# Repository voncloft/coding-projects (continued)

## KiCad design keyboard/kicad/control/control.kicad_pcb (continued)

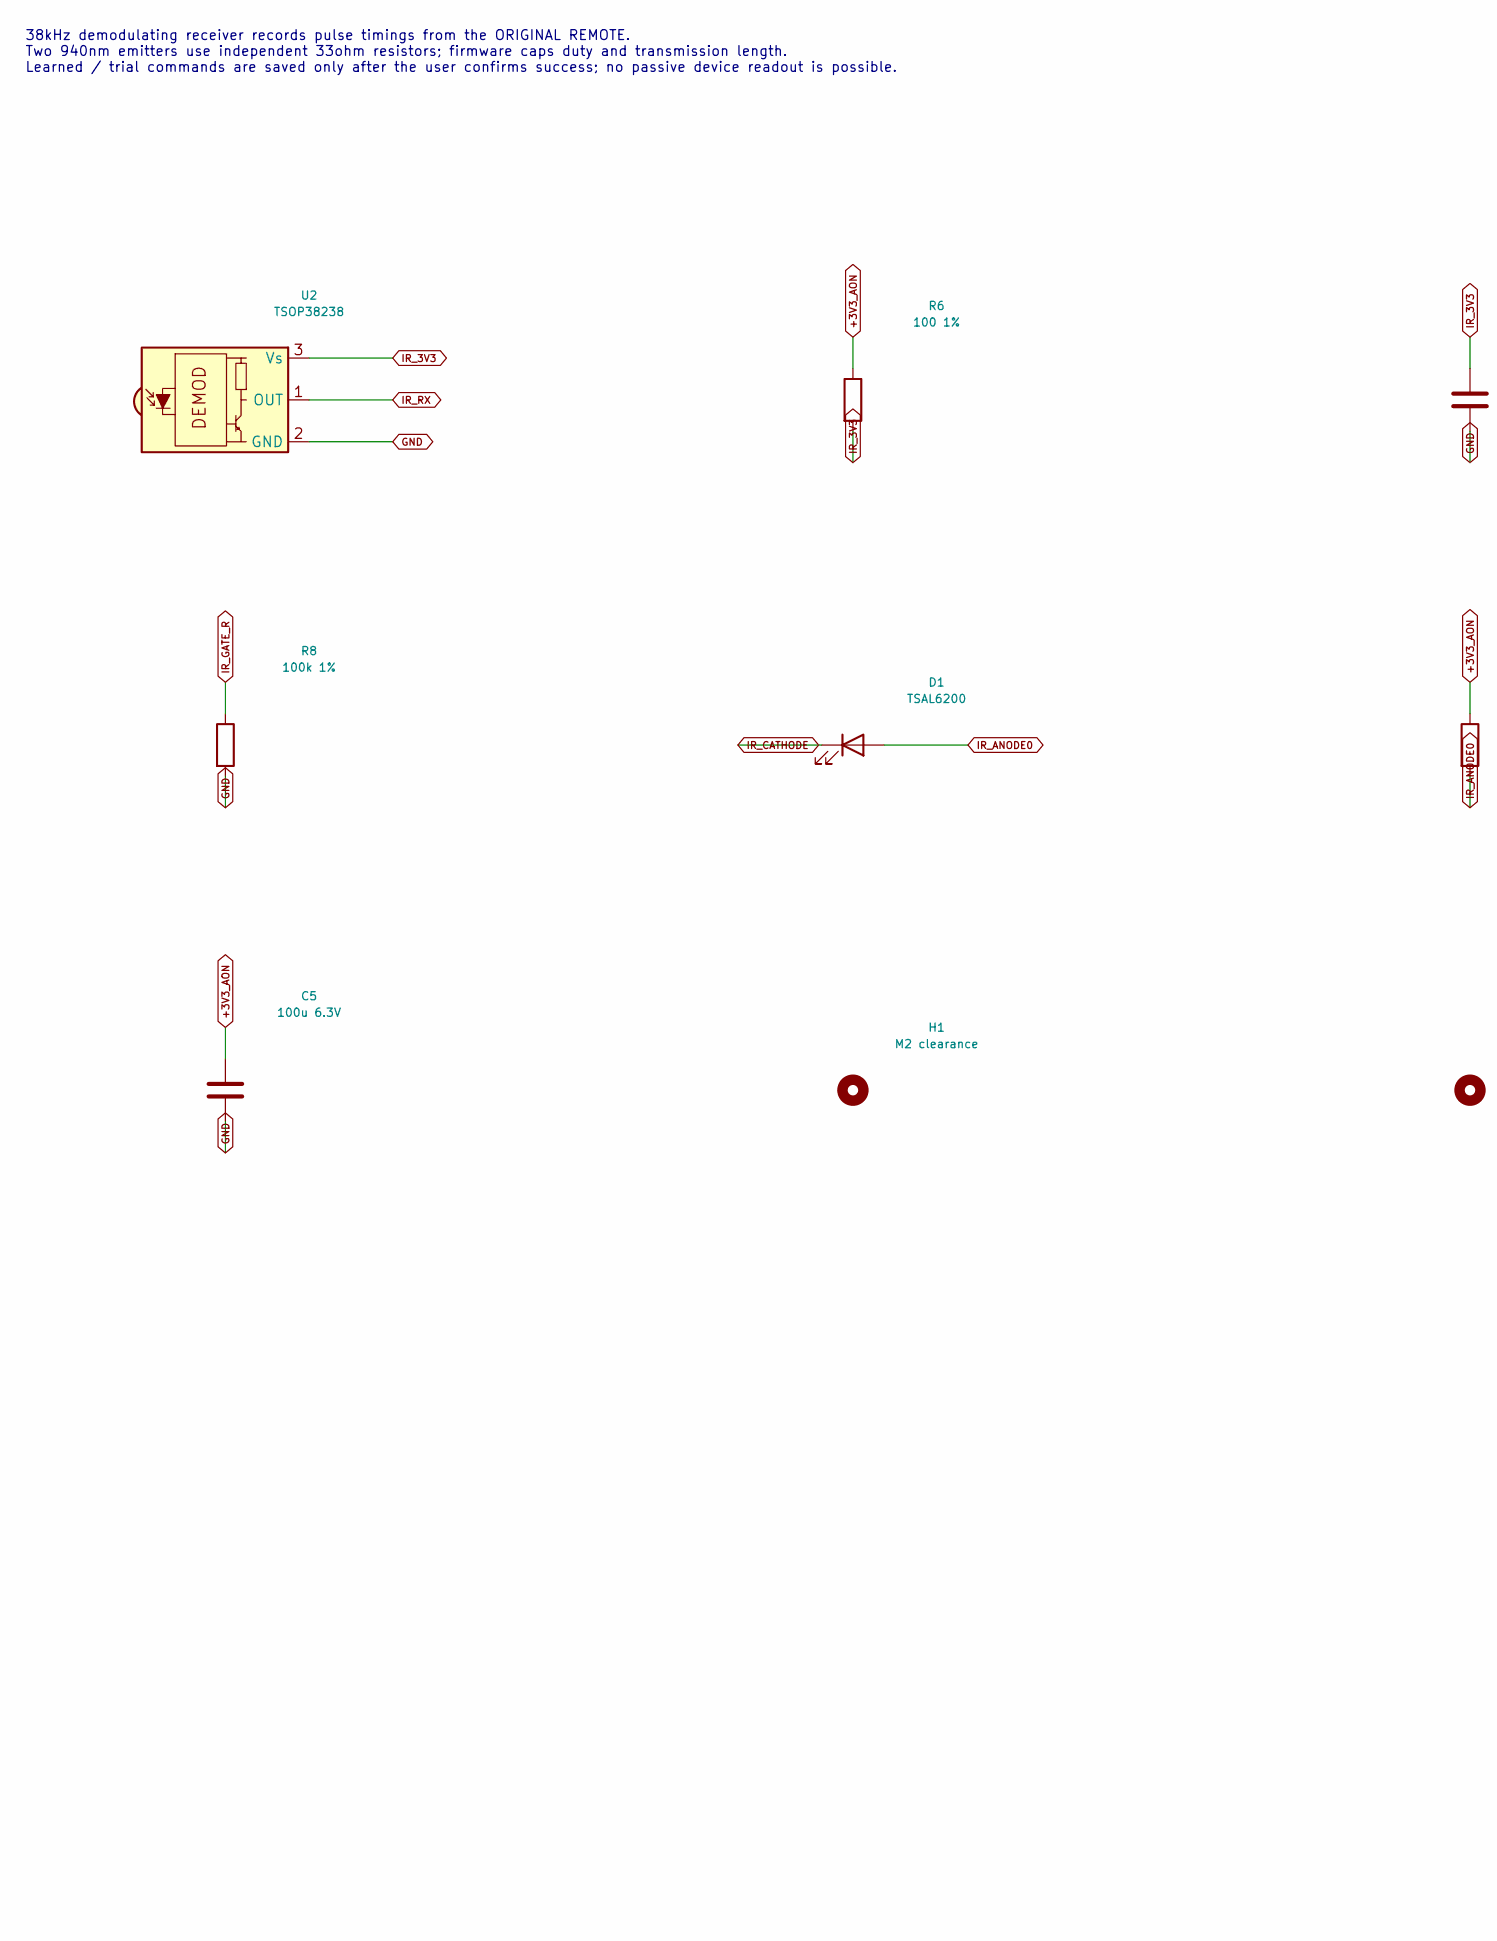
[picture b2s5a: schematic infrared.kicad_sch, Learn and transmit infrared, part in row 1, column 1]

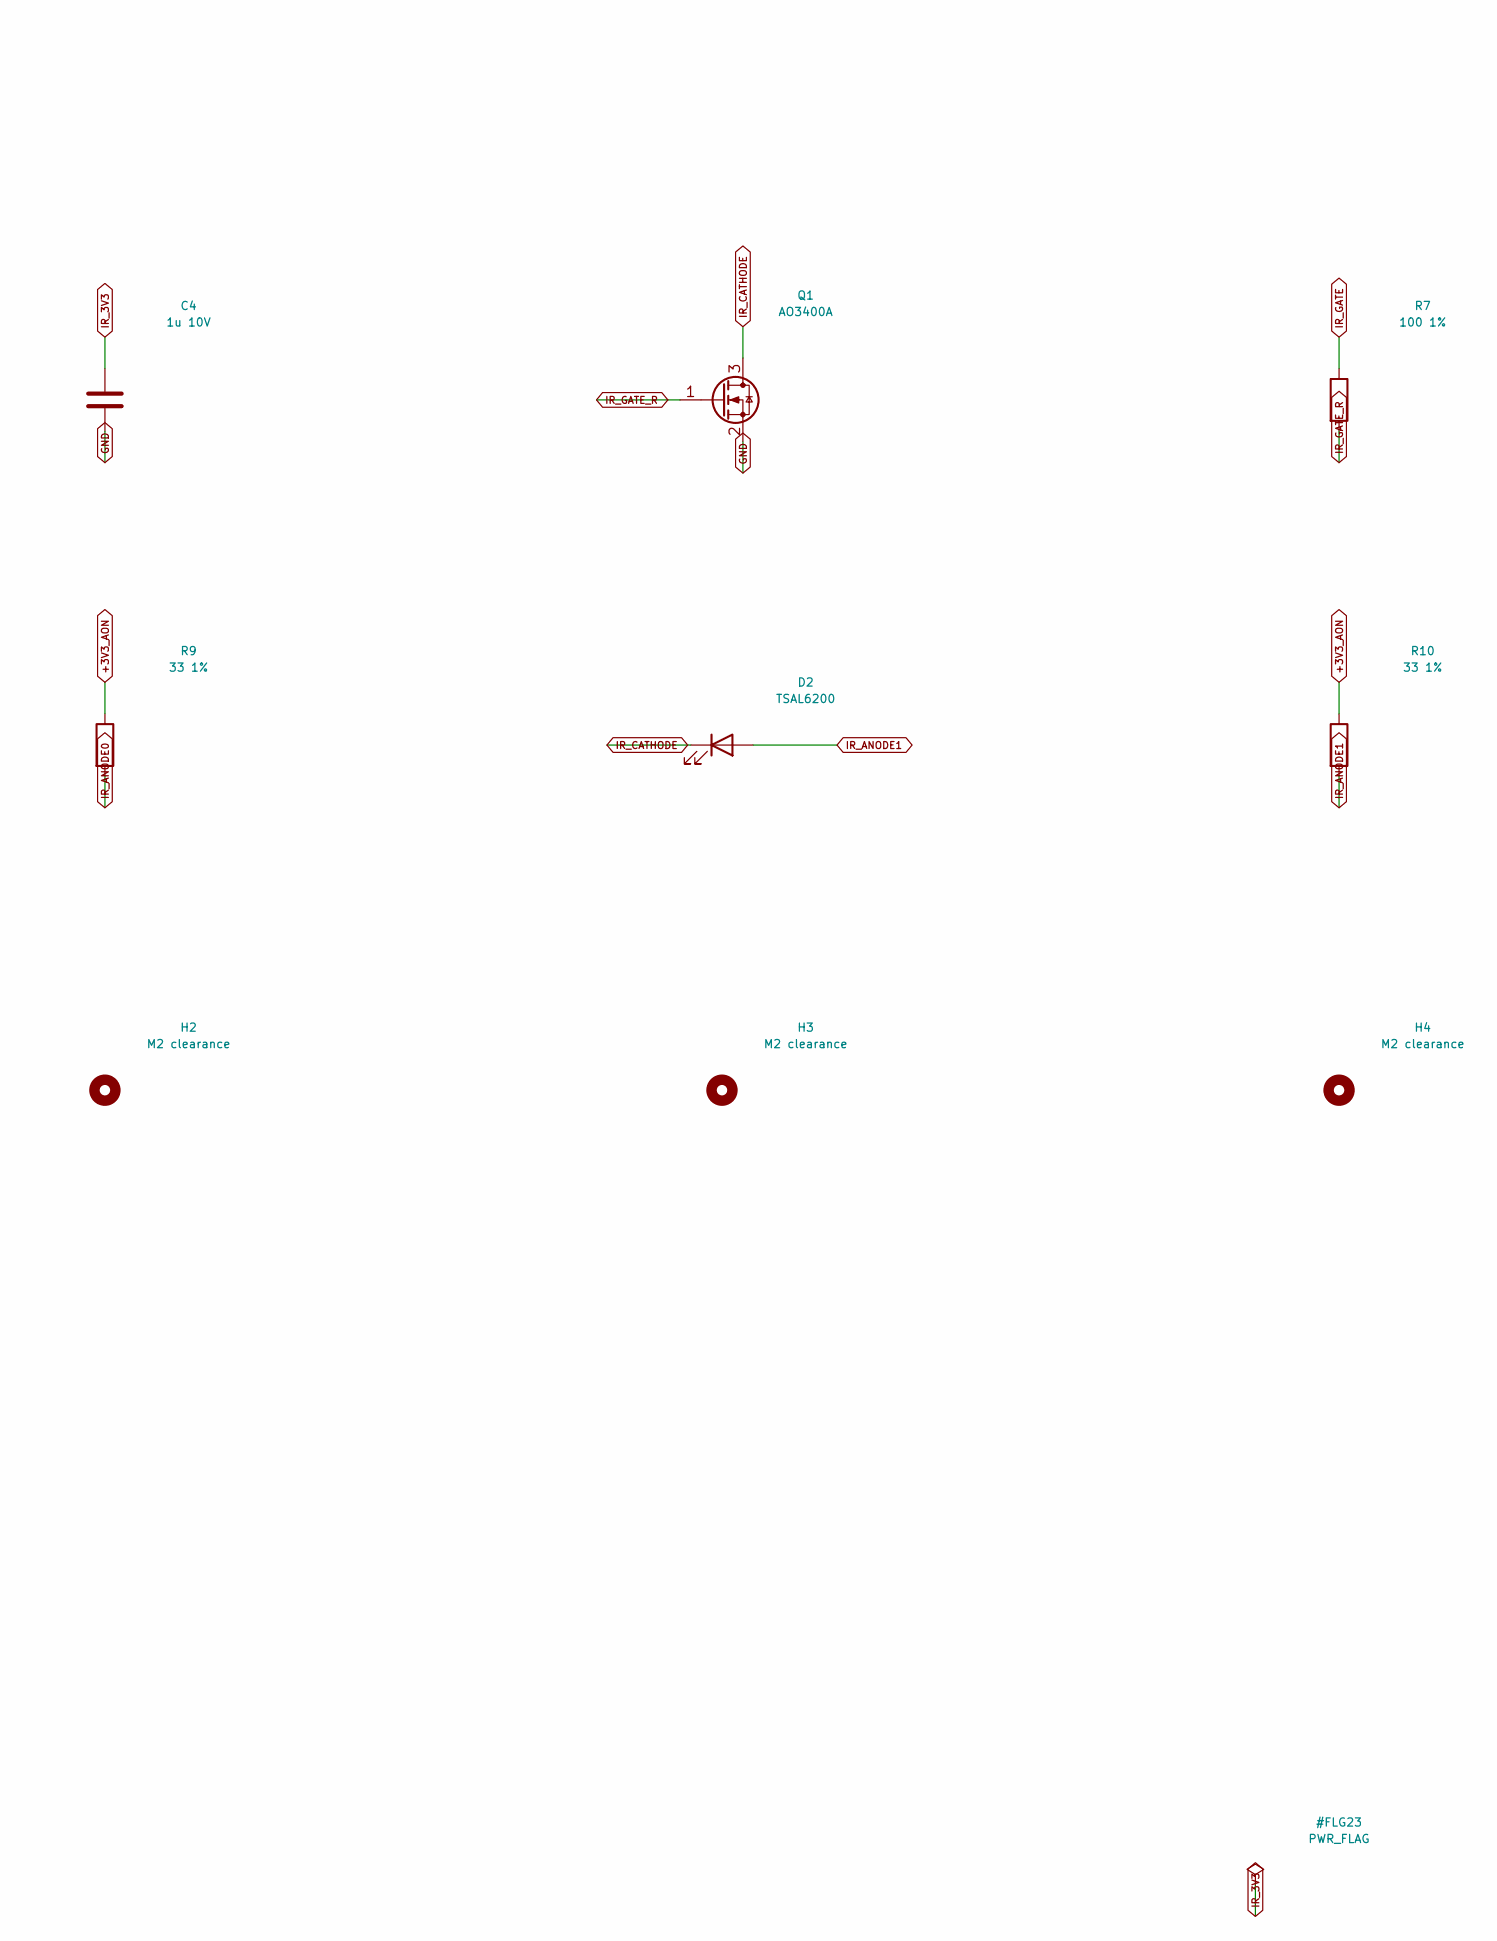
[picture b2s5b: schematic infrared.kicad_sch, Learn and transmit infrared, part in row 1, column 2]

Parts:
C4: 1u 10V; C_0603_1608Metric
C5: 100u 6.3V; C_1210_3225Metric; MPN GRM32ER60J107ME20L
D1, D2: TSAL6200; LED_D5.0mm_Horizontal_O1.27mm_Z3.0mm; MPN TSAL6200
H1, H2, H3, H4: M2 clearance; MountingHole_2.2mm_M2
Q1: AO3400A; SOT-23; MPN AO3400A
R6, R7: 100 1%; R_0603_1608Metric
R8: 100k 1%; R_0603_1608Metric
R9, R10: 33 1%; R_0603_1608Metric
U2: TSOP38238; Vishay_MINICAST-3Pin; MPN TSOP38238

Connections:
+3V3_AON: C5.1, R6.1, R9.1, R10.1; also elsewhere on the board
GND: C4.2, C5.2, Q1.2 (S), R8.2, U2.2 (GND); also elsewhere on the board
IR_3V3: C4.1, R6.2, U2.3 (Vs)
IR_ANODE0: D1.2 (A), R9.2
IR_ANODE1: D2.2 (A), R10.2
IR_CATHODE: D1.1 (K), D2.1 (K), Q1.3 (D)
IR_GATE: R7.1; also elsewhere on the board
IR_GATE_R: Q1.1 (G), R7.2, R8.1
IR_RX: U2.1 (OUT); also elsewhere on the board

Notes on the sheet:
38kHz demodulating receiver records pulse timings from the ORIGINAL REMOTE. Two 940nm emitters use independent 33ohm resistors; firmware caps duty and transmission length. Learned / trial commands are saved only after the user confirms success; no passive device readout is possible.

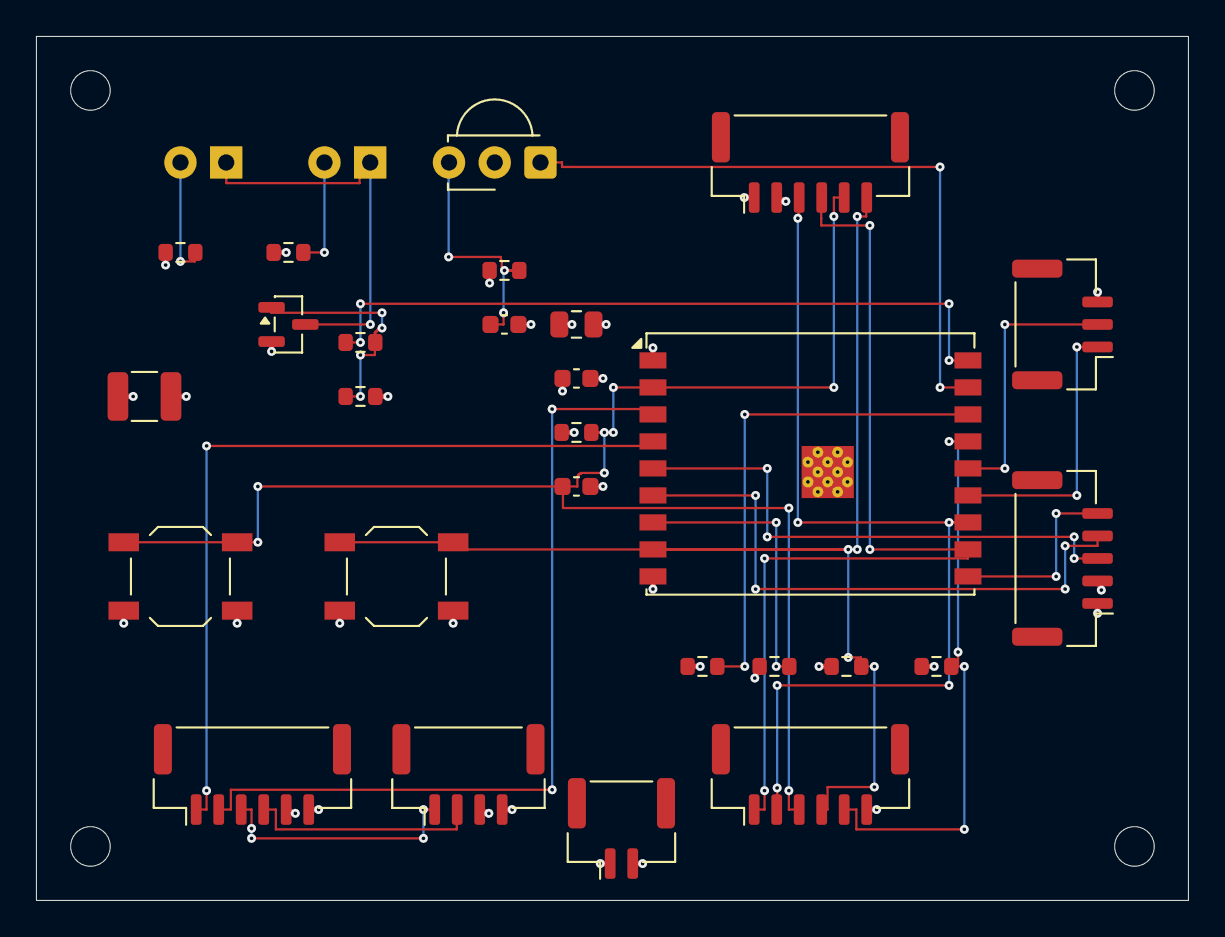
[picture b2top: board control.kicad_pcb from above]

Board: 4 copper layers, 64.0 x 48.0 mm, 33 parts (0 on the bottom side), 25 nets.

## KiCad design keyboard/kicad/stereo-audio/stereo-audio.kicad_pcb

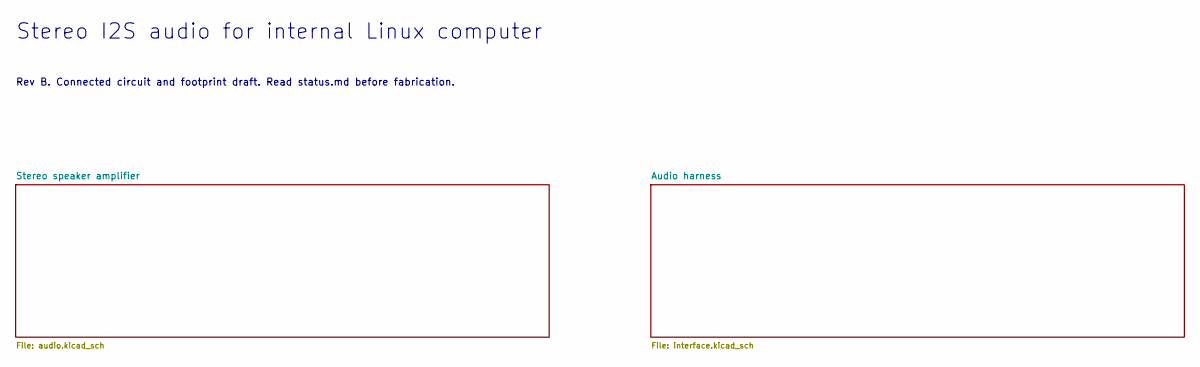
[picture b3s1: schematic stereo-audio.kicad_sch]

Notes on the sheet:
Stereo I2S audio for internal Linux computer
Rev B. Connected circuit and footprint draft. Read status.md before fabrication.

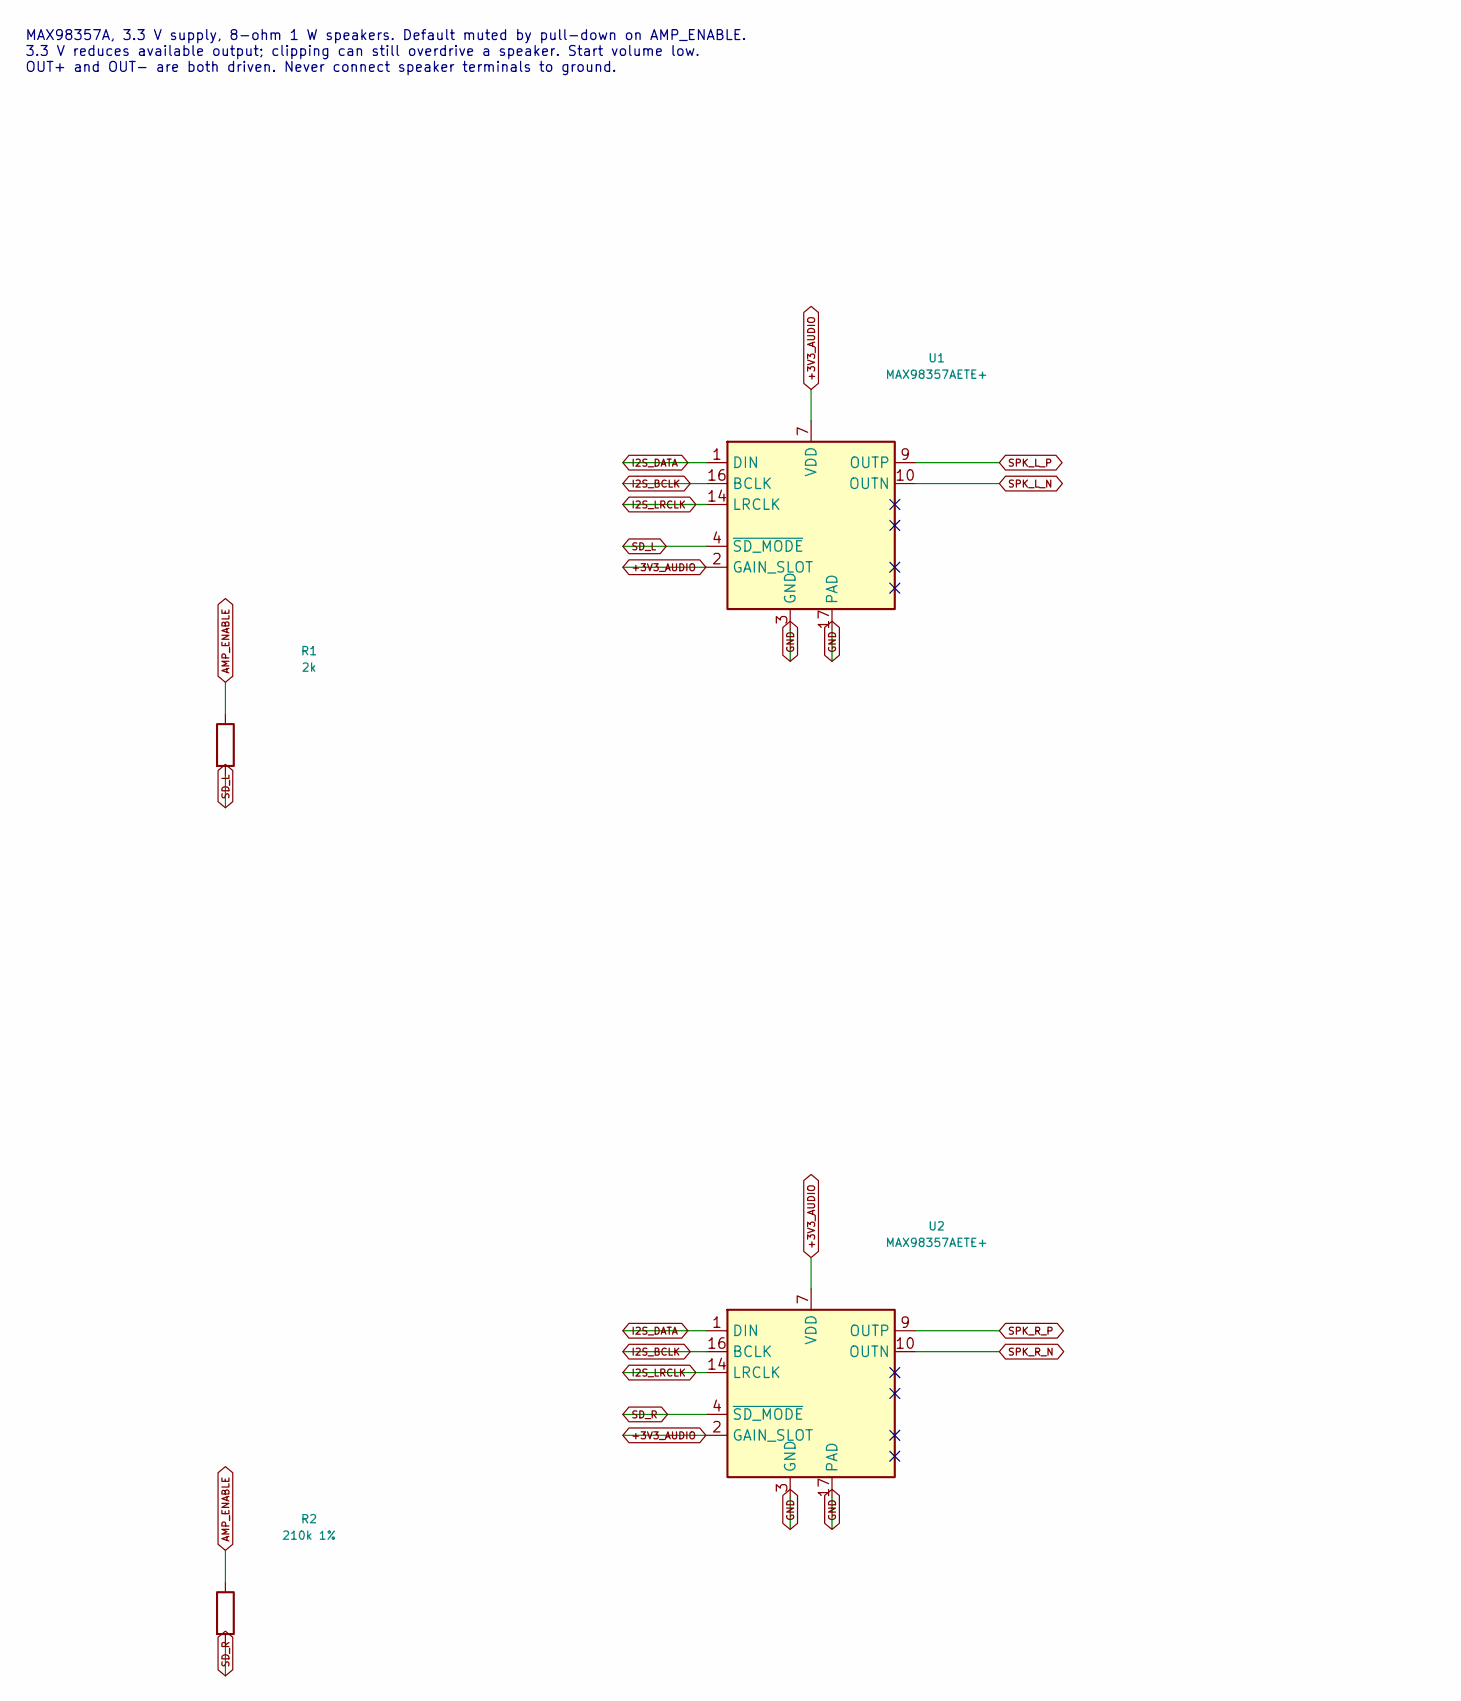
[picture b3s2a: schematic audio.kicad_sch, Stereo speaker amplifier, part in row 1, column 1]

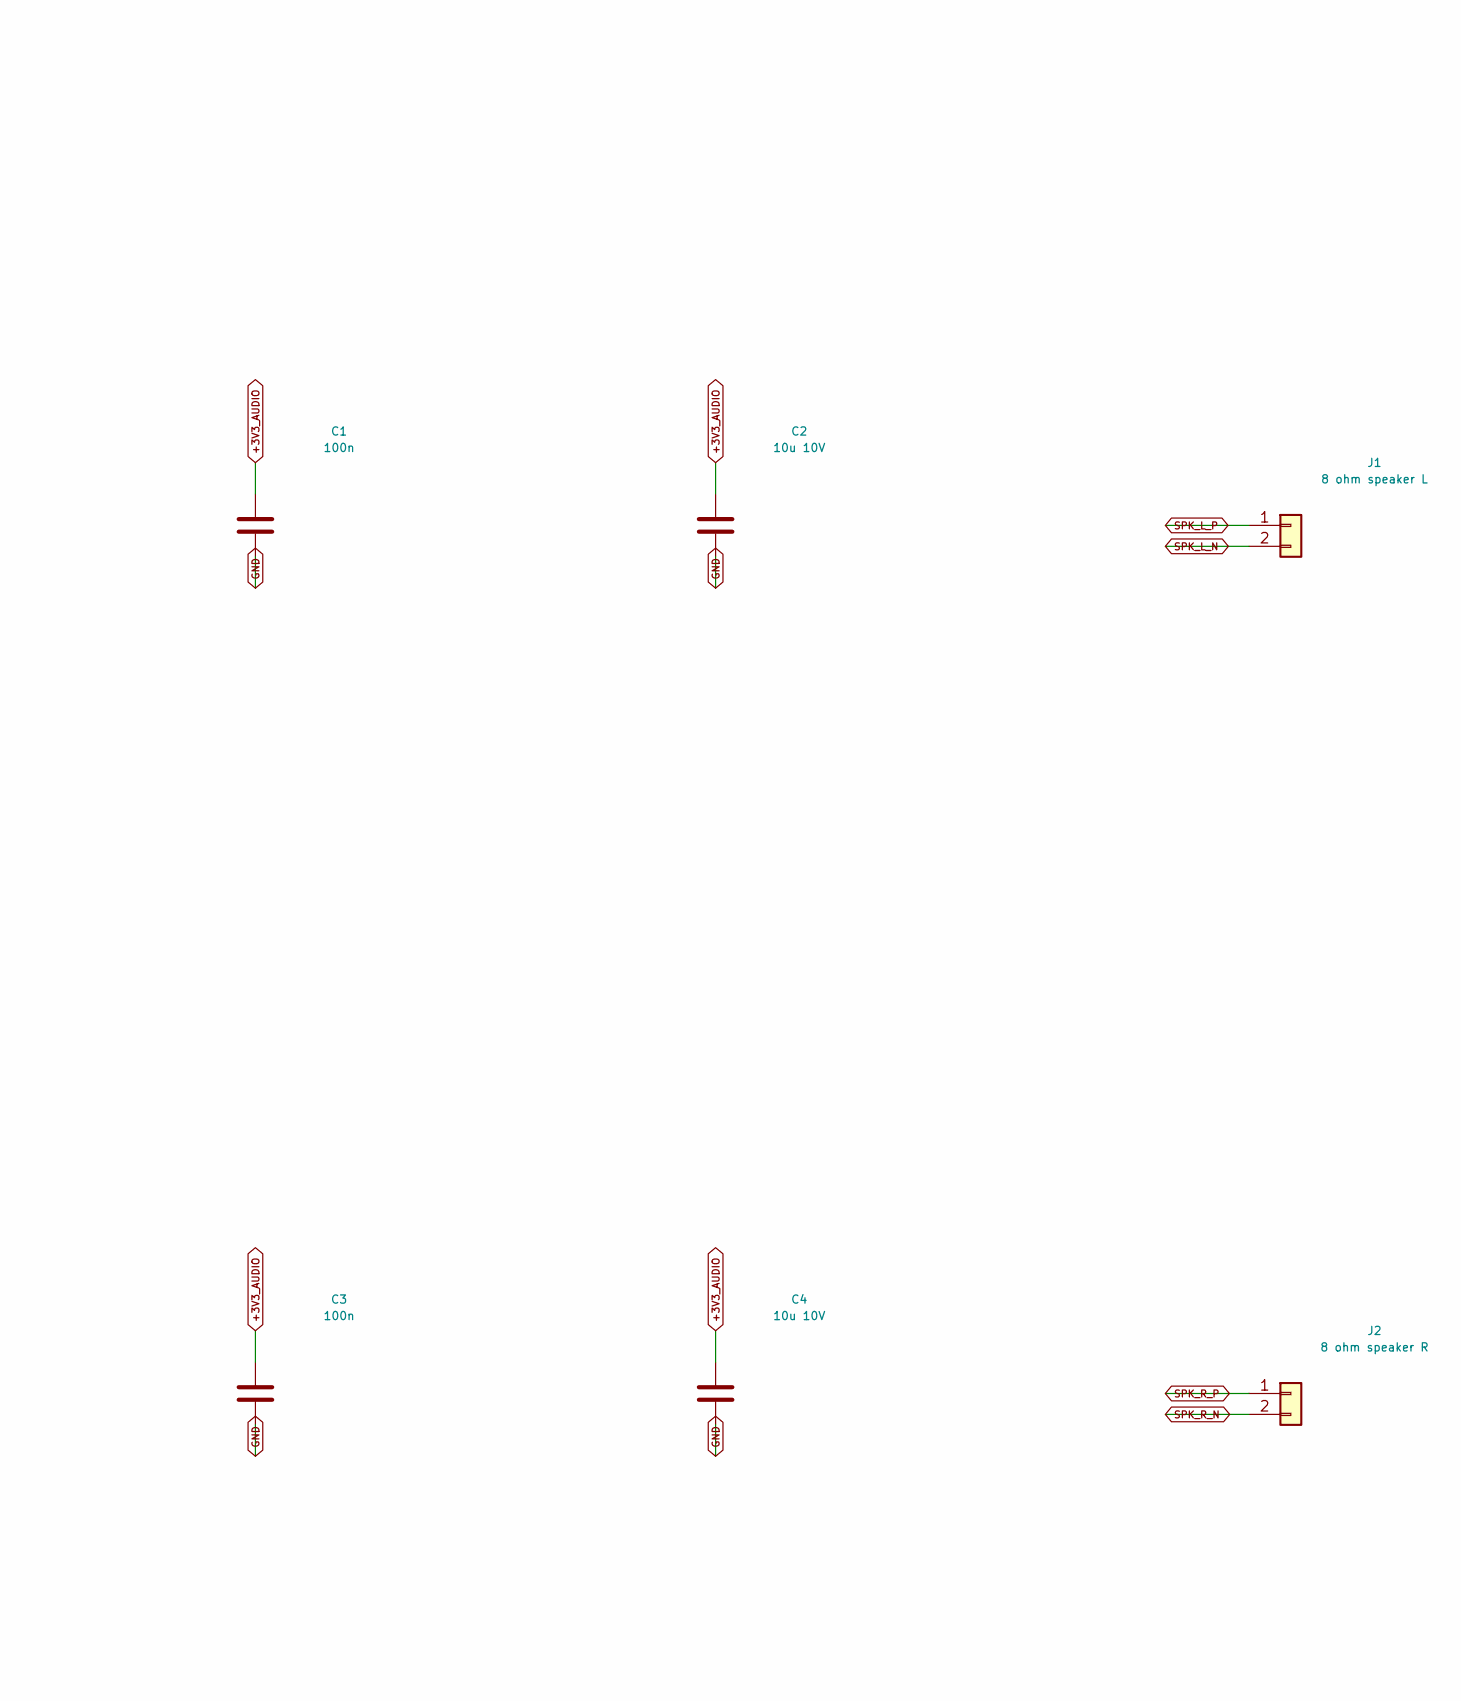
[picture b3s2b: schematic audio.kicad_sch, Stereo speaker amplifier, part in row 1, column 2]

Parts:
C1, C3: 100n; C_0603_1608Metric
C2, C4: 10u 10V; C_0805_2012Metric
J1: 8 ohm speaker L; Molex_PicoBlade_53261-0271_1x02-1MP_P1.25mm_Horizontal; MPN 53261-0271
J2: 8 ohm speaker R; Molex_PicoBlade_53261-0271_1x02-1MP_P1.25mm_Horizontal; MPN 53261-0271
R1: 2k; R_0603_1608Metric
R2: 210k 1%; R_0603_1608Metric
U1, U2: MAX98357AETE+; TQFN-16-1EP_3x3mm_P0.5mm_EP1.6x1.6mm; MPN MAX98357AETE+

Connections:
+3V3_AUDIO: C1.1, C2.1, C3.1, C4.1, U1.2 (GAIN_SLOT), U1.7 (VDD), U1.8 (VDD), U2.2 (GAIN_SLOT), U2.7 (VDD), U2.8 (VDD); also elsewhere on the board
AMP_ENABLE: R1.1, R2.1; also elsewhere on the board
GND: C1.2, C2.2, C3.2, C4.2, U1.3 (GND), U1.11 (GND), U1.15 (GND), U1.17 (PAD), U2.3 (GND), U2.11 (GND), U2.15 (GND), U2.17 (PAD); also elsewhere on the board
I2S_BCLK: U1.16 (BCLK), U2.16 (BCLK); also elsewhere on the board
I2S_DATA: U1.1 (DIN), U2.1 (DIN); also elsewhere on the board
I2S_LRCLK: U1.14 (LRCLK), U2.14 (LRCLK); also elsewhere on the board
SD_L: R1.2, U1.4 (~SD_MODE)
SD_R: R2.2, U2.4 (~SD_MODE)
SPK_L_N: J1.2, U1.10 (OUTN)
SPK_L_P: J1.1, U1.9 (OUTP)
SPK_R_N: J2.2, U2.10 (OUTN)
SPK_R_P: J2.1, U2.9 (OUTP)

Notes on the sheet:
MAX98357A, 3.3 V supply, 8-ohm 1 W speakers. Default muted by pull-down on AMP_ENABLE. 3.3 V reduces available output; clipping can still overdrive a speaker. Start volume low. OUT+ and OUT- are both driven. Never connect speaker terminals to ground.

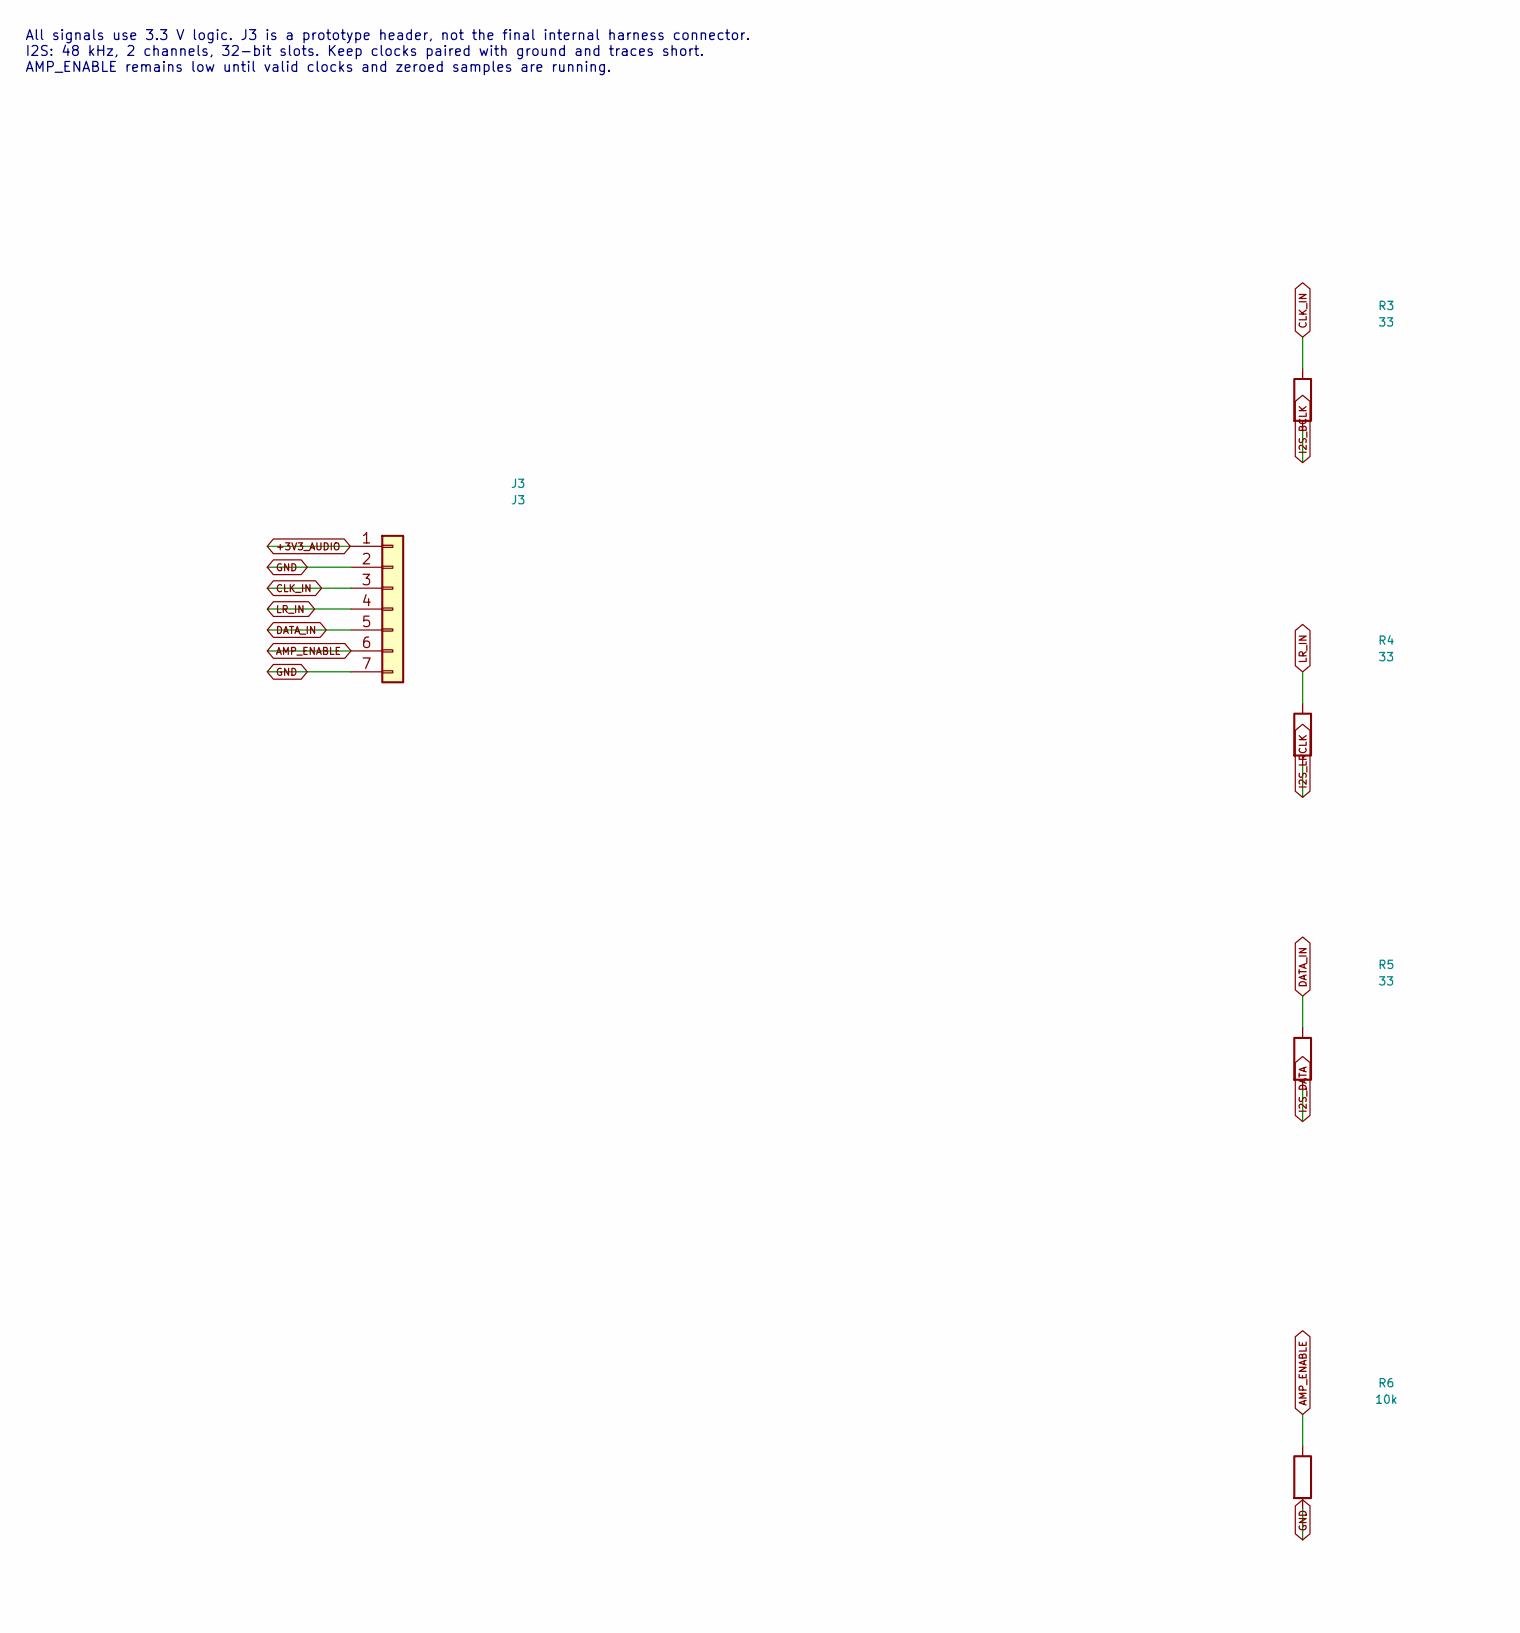
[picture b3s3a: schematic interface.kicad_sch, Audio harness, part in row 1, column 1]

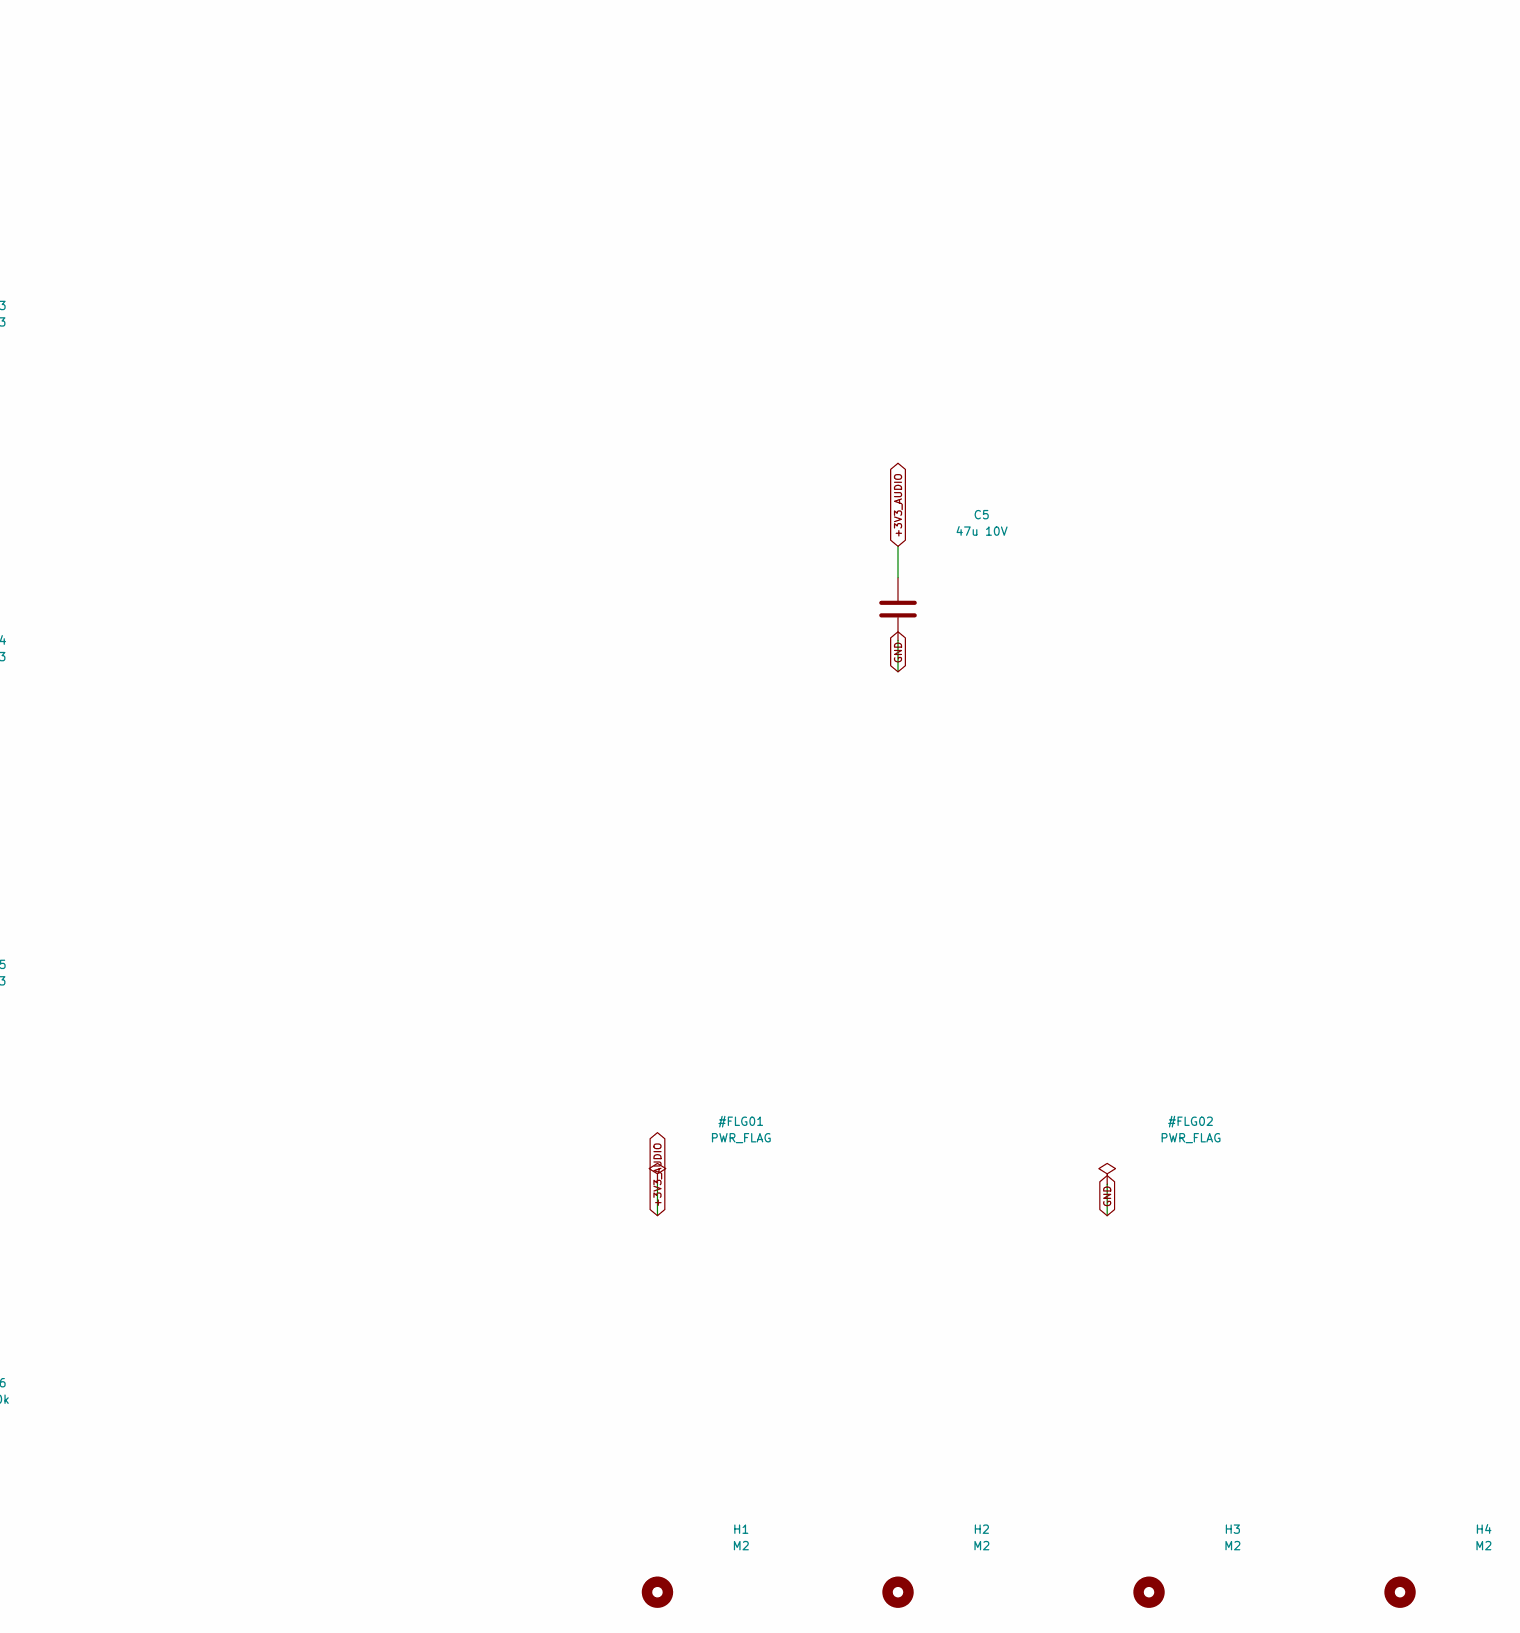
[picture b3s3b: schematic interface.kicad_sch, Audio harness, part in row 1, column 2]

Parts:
C5: 47u 10V; C_1210_3225Metric
H1, H2, H3, H4: M2; MountingHole_2.2mm_M2
J3: J3; PinHeader_1x07_P2.54mm_Vertical
R3, R4, R5: 33; R_0603_1608Metric
R6: 10k; R_0603_1608Metric

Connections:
+3V3_AUDIO: C5.1, J3.1; also elsewhere on the board
AMP_ENABLE: J3.6, R6.1; also elsewhere on the board
CLK_IN: J3.3, R3.1
DATA_IN: J3.5, R5.1
GND: C5.2, J3.2, J3.7, R6.2; also elsewhere on the board
I2S_BCLK: R3.2; also elsewhere on the board
I2S_DATA: R5.2; also elsewhere on the board
I2S_LRCLK: R4.2; also elsewhere on the board
LR_IN: J3.4, R4.1

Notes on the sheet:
All signals use 3.3 V logic. J3 is a prototype header, not the final internal harness connector. I2S: 48 kHz, 2 channels, 32-bit slots. Keep clocks paired with ground and traces short. AMP_ENABLE remains low until valid clocks and zeroed samples are running.

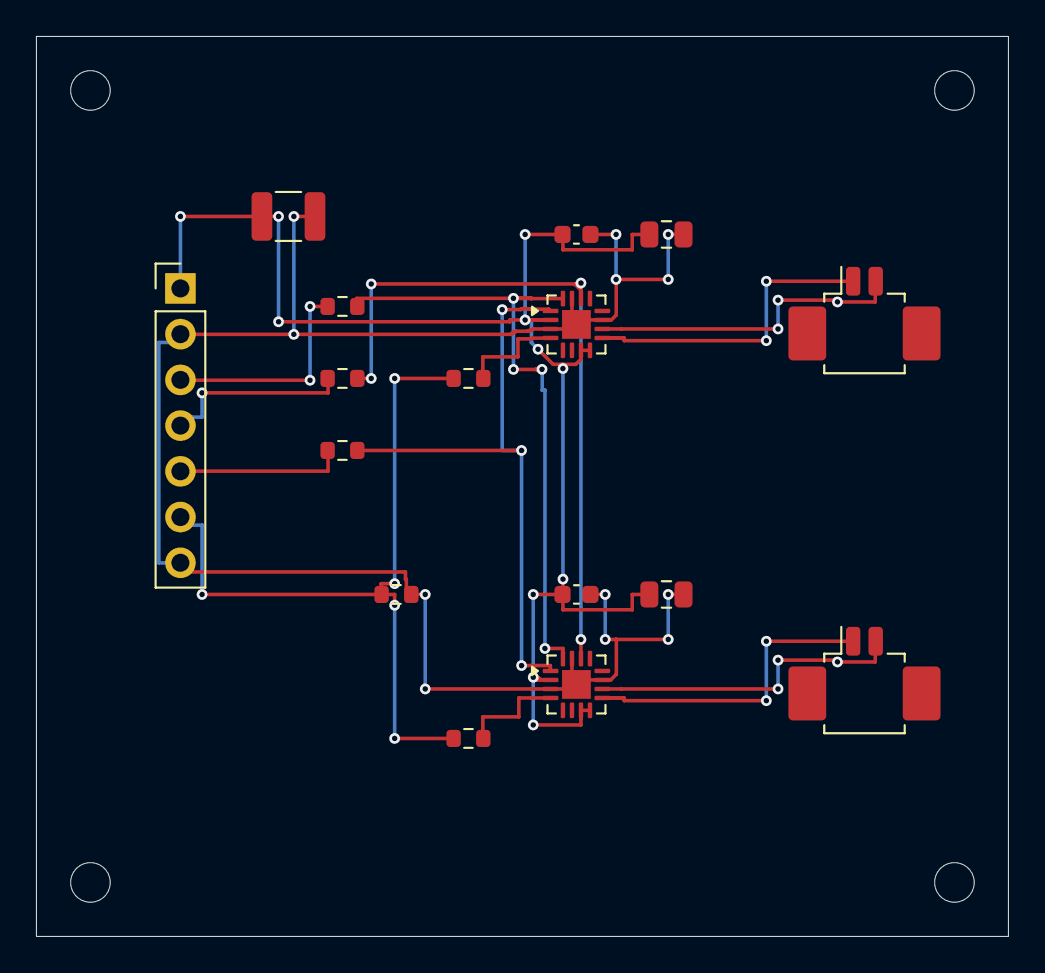
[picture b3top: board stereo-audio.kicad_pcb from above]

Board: 2 copper layers, 54.0 x 50.0 mm, 20 parts (0 on the bottom side), 15 nets.

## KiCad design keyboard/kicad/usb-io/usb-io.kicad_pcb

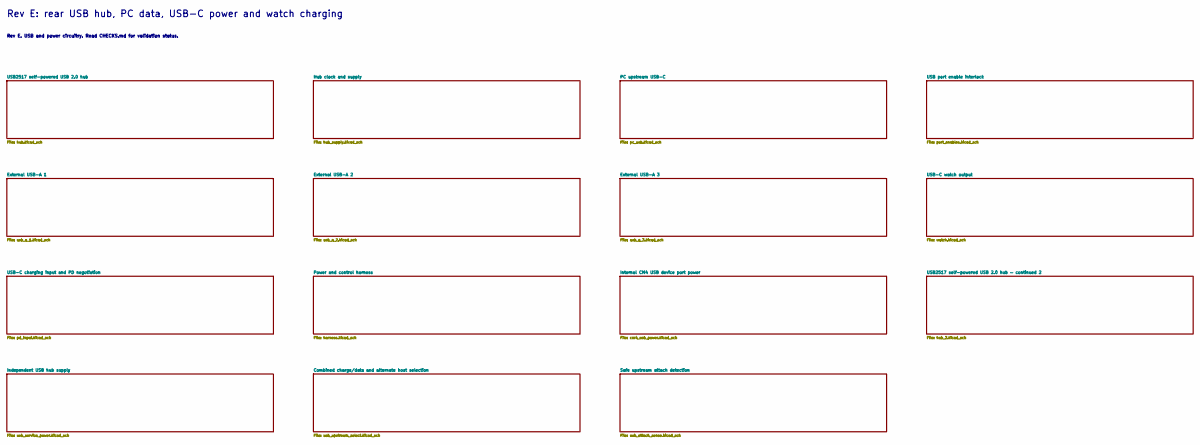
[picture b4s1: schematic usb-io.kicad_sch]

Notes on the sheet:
Rev E: rear USB hub, PC data, USB-C power and watch charging
Rev E. USB and power circuitry. Read CHECKS.md for validation status.
